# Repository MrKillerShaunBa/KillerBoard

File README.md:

# KillerBoard
Welcome to KillerBoard, a 65% wireless hot-swappable mechanical keyboard which is made in a sandwich mounted style. It has a 3d printed case, custom PCB and a ProMicro controller for it brains.

I got the motivation to make this when I saw other cool keyboards the people have built for ``#Highway``. Also, I loved making my [Hackpad](https://github.com/MrKillerShaunBa/BajajPad) and wanted to try making something which was bigger, better and wireless of-course.

## Featues

- 65% compact layout
- Wireless, uses Promicro Controller
- ZMK firmware
- Hotswappable
- Brown tactile switches
- 6 deg typing angle
- 3D Printed case and plate
- Sandwich mount

## CAD

## PCB

## ZMK Keymap 

### BOM

| Product | Quantity | Source | Price(INR) | Price($) | Link |
| :-----: | :-----: | :-----: | :-----: | :-----: | :-----: |
| Keycaps | 1 | StacksKB | 1299 | 15.10 | [here](https://stackskb.com/store/veekos-gradient-keycaps-cherry-profile-135-keys/) |
| MX Style Switches | 25*3 | Genesispc | 2400 | 27.91 | [here](https://www.genesispc.in/products/c-equalz-x-tkc-kiwi-switches?variant=43389284286517) |
| Stabilizers | 1 | StacksKB | 1595 | 18.55 | [here](https://stackskb.com/store/durock-smokey-screw-in-stabilizers-v2/) |
| PCB | 5 | JLCPCB | | 11.05 | Includes Shipping (Used Coupon) |
| Case | 1 | Printing Legion | - | ~5 | Only shipping |
| Hotswap Sockets | 10*7 | Meckeys | 536 | 6.23 | [here](https://meckeys.com/shop/accessories/keyboard-accessories/key-switches/kailh-hot-swap-socket/) |
| 1N4148 Diodes | 10*7 | StacksKB | 105 | 1.22 | [here](https://stackskb.com/store/1n4148-through-hole-diode/) |
| ProMicro nRF52840 | 1 | Robu.in | 715 | 8.33| [here](https://robu.in/product/promicro-nrf52840-development-board/) |
| Slide Switch | 1 | Robu.in | 3 | 0.035 | [here](https://robu.in/product/ss-12f21g5-slide-1p2t-angled-switchheight5mm/) |
| Battery | 1 | Robu.in | 256 | 2.97 | [here](https://robu.in/product/wly602540-600mah-3-7v-single-cell-rechargeable-lipo-battery/) |
| PCB receptacle female | 1 | Amazon | 135 | 1.57 | [here](https://amzn.in/d/0Ydhh59) |
| PCB receptacle male | 2 | Robu.in | 68 | 0.79 | [here](https://robu.in/product/361019115sg107601-jiln-2-54x1-9machined-pin-header-1x15p-180-l7-65-upper-pinpoint0-46-bottom-pinpoint0-46-au1u-pps/) |
| Non-slip feet | 100 | Amazon | 130 | 1.51 | [here](https://amzn.in/d/hfOWean) |
| M3x25mm bolts | 12 | Robu | 167 | 1.93 | [here](https://robu.in/product/easymech-set-m3-x-25mm-socket-head-cap-allen-bolt-nut-12-pcs/) |
| M3x15mm bolts | 10 | EDS | 139  | 1.61 | [here](https://store.edsystems.in/thunderbolt-set-of-m3-x-15mm-socket-head-cap-black-(allen)-bolt-and-nut-(10-pcs)) | M3x4mm heatset insert | 25 | Robu | 82 | 0.95 | [here](https://robu.in/product/m3-x-4-mm-brass-heat-set-knurl-threaded-round-insert-nut-25-pcs/) |
| M3x4mm heatset inserts | 25 | Robu | 82 | 0.95 | [here](https://robu.in/product/m3-x-4-mm-brass-heat-set-knurl-threaded-round-insert-nut-25-pcs/) |

Total Cost: About $108-110

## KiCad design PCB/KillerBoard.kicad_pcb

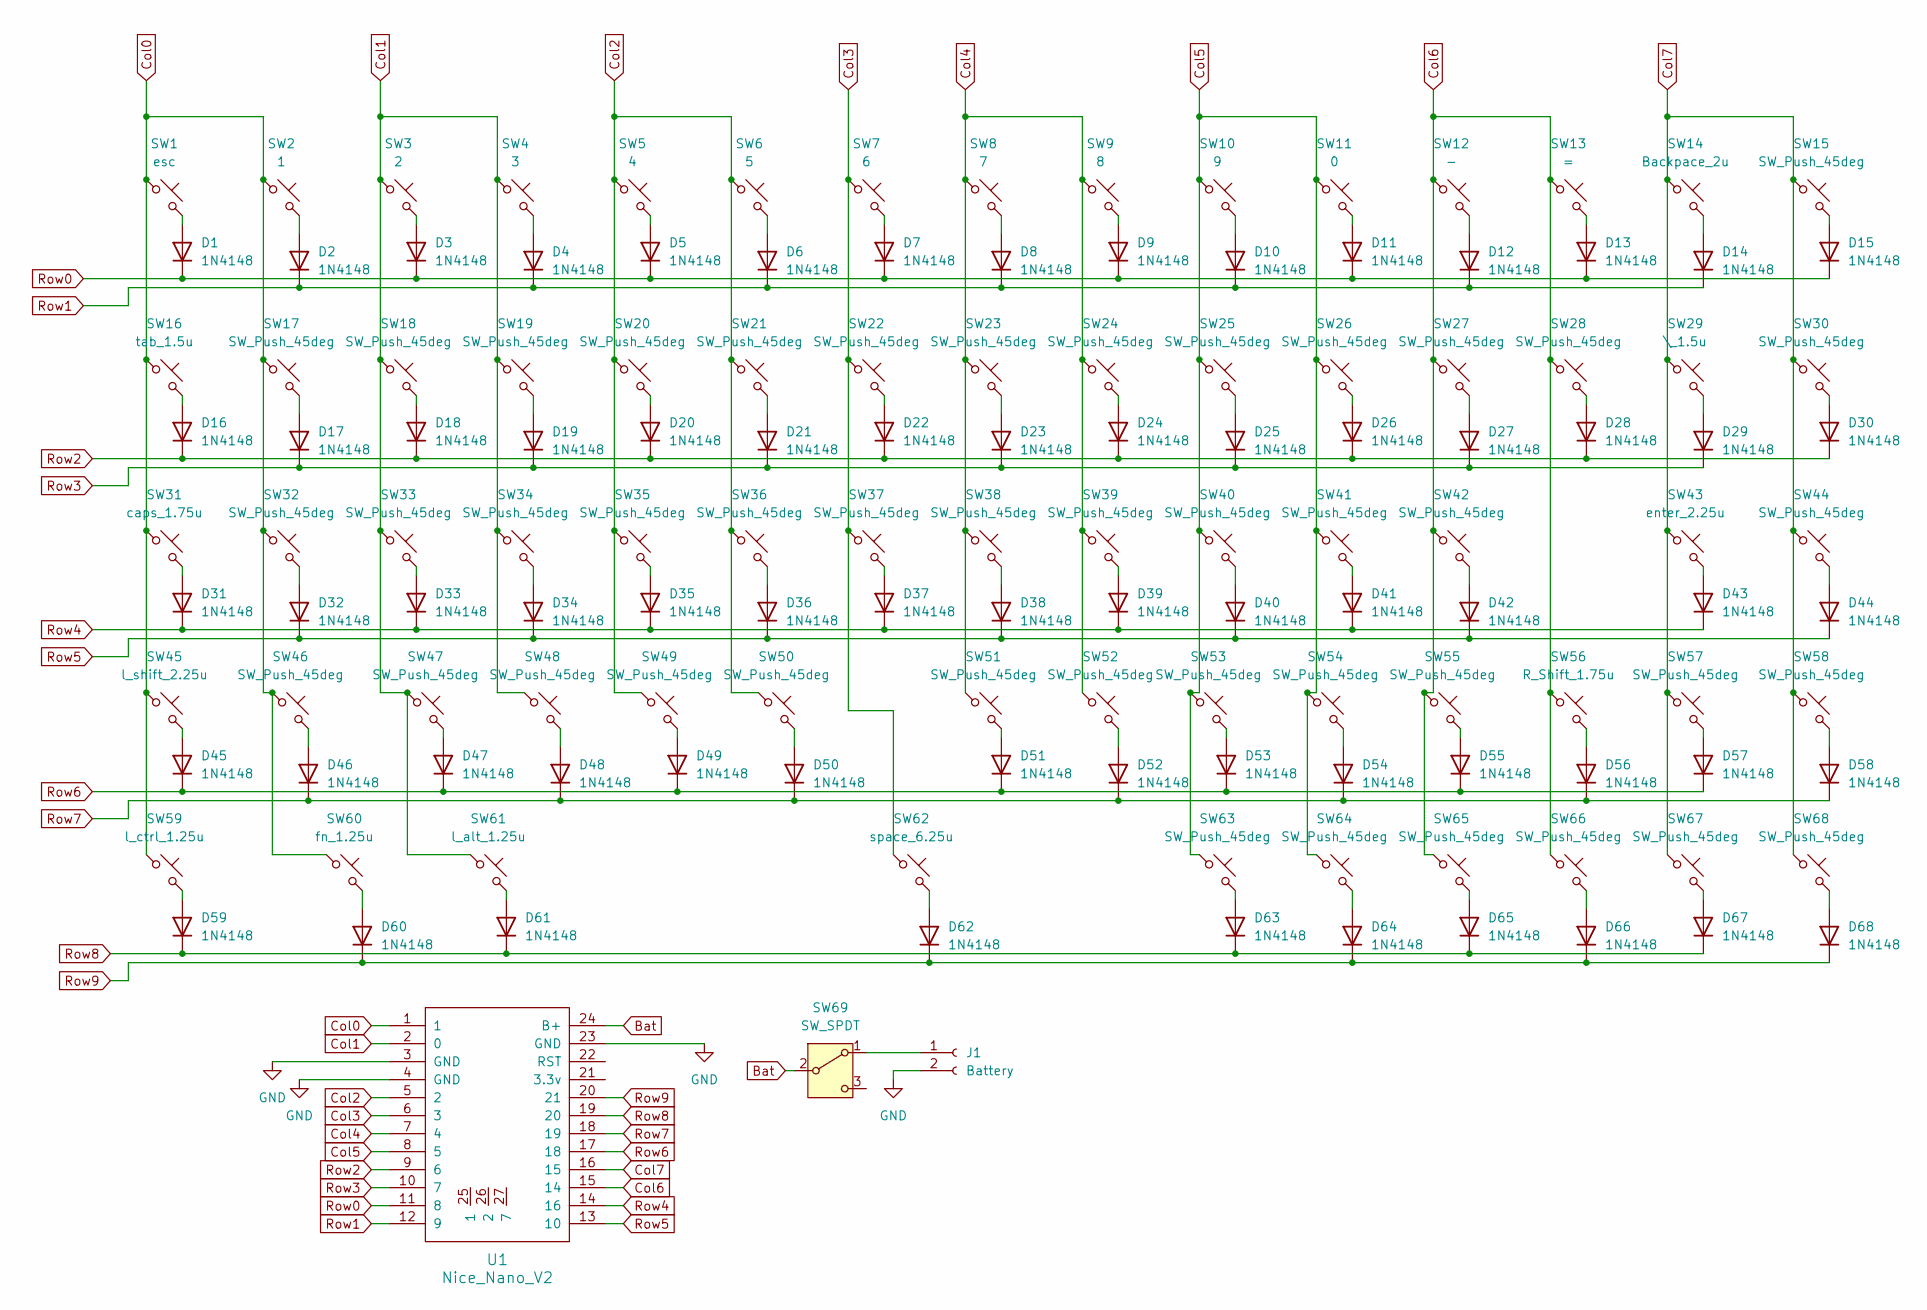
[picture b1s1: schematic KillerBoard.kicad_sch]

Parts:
D1, D2, D3, D4, D5, D6, D7, D8, D9, D10, D11, D12, D13, D14, D15, D16, D17, D18, D19, D20, D21, D22, D23, D24, D25, D26, D27, D28, D29, D30, D31, D32, D33, D34, D35, D36, D37, D38, D39, D40, D41, D42, D43, D44, D45, D46, D47, D48, D49, D50, D51, D52, D53, D54, D55, D56, D57, D58, D59, D60, D61, D62, D63, D64, D65, D66, D67, D68: 1N4148; D_DO-35_SOD27_P7.62mm_Horizontal
J1: Battery
SW1: esc; Hotswap_MX_Plated_1.00u
SW2: 1; Hotswap_MX_Plated_1.00u
SW3: 2; Hotswap_MX_Plated_1.00u
SW4: 3; Hotswap_MX_Plated_1.00u
SW5: 4; Hotswap_MX_Plated_1.00u
SW6: 5; Hotswap_MX_Plated_1.00u
SW7: 6; Hotswap_MX_Plated_1.00u
SW8: 7; Hotswap_MX_Plated_1.00u
SW9: 8; Hotswap_MX_Plated_1.00u
SW10: 9; Hotswap_MX_Plated_1.00u
SW11: 0; Hotswap_MX_Plated_1.00u
SW12: -; Hotswap_MX_Plated_1.00u
SW13: =; Hotswap_MX_Plated_1.00u
SW14: Backpace_2u; MX_Hotswap_2.00u
SW15, SW17, SW18, SW19, SW20, SW21, SW22, SW23, SW24, SW25, SW26, SW27, SW28, SW30, SW32, SW33, SW34, SW35, SW36, SW37, SW38, SW39, SW40, SW41, SW42, SW44, SW46, SW47, SW48, SW49, SW50, SW51, SW52, SW53, SW54, SW55, SW57, SW58, SW63, SW64, SW65, SW66, SW67, SW68: SW_Push_45deg; Hotswap_MX_Plated_1.00u
SW16: tab_1.5u; Hotswap_MX_Plated_1.50u
SW29: \_1.5u; Hotswap_MX_Plated_1.50u
SW31: caps_1.75u; Hotswap_MX_Plated_1.75u
SW43: enter_2.25u; MX_Hotswap_2.25u
SW45: l_shift_2.25u; MX_Hotswap_2.25u
SW56: R_Shift_1.75u; Hotswap_MX_Plated_1.75u
SW59: l_ctrl_1.25u; Hotswap_MX_Plated_1.25u
SW60: fn_1.25u; Hotswap_MX_Plated_1.25u
SW61: l_alt_1.25u; Hotswap_MX_Plated_1.25u
SW62: space_6.25u; MX_Hotswap_6.25u
SW69: SW_SPDT; Switch_K3-1204D
U1: Nice_Nano_V2

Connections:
Bat: SW69.2 (B), U1.24 (B+)
Col0: SW1.1, SW2.1, SW16.1, SW17.1, SW31.1, SW32.1, SW45.1, SW46.1, SW59.1, SW60.1, U1.1
Col1: SW3.1, SW4.1, SW18.1, SW19.1, SW33.1, SW34.1, SW47.1, SW48.1, SW61.1, U1.2 (0)
Col2: SW5.1, SW6.1, SW20.1, SW21.1, SW35.1, SW36.1, SW49.1, SW50.1, U1.5 (2)
Col3: SW7.1, SW22.1, SW37.1, SW62.1, U1.6 (3)
Col4: SW8.1, SW9.1, SW23.1, SW24.1, SW38.1, SW39.1, SW51.1, SW52.1, U1.7 (4)
Col5: SW10.1, SW11.1, SW25.1, SW26.1, SW40.1, SW41.1, SW53.1, SW54.1, SW63.1, SW64.1, U1.8 (5)
Col6: SW12.1, SW13.1, SW27.1, SW28.1, SW42.1, SW55.1, SW56.1, SW65.1, SW66.1, U1.15 (14)
Col7: SW14.1, SW15.1, SW29.1, SW30.1, SW43.1, SW44.1, SW57.1, SW58.1, SW67.1, SW68.1, U1.16 (15)
GND: J1.2, U1.3 (GND), U1.4 (GND), U1.23 (GND)
unnamed: D1.2 (A), SW1.2
unnamed: D2.2 (A), SW2.2
unnamed: D3.2 (A), SW3.2
unnamed: D4.2 (A), SW4.2
unnamed: D5.2 (A), SW5.2
unnamed: D6.2 (A), SW6.2
unnamed: D7.2 (A), SW7.2
unnamed: D8.2 (A), SW8.2
unnamed: D9.2 (A), SW9.2
unnamed: D10.2 (A), SW10.2
unnamed: D11.2 (A), SW11.2
unnamed: D12.2 (A), SW12.2
unnamed: D13.2 (A), SW13.2
unnamed: D14.2 (A), SW14.2
unnamed: D15.2 (A), SW15.2
unnamed: D16.2 (A), SW16.2
unnamed: D17.2 (A), SW17.2
unnamed: D18.2 (A), SW18.2
unnamed: D19.2 (A), SW19.2
unnamed: D20.2 (A), SW20.2
unnamed: D21.2 (A), SW21.2
unnamed: D22.2 (A), SW22.2
unnamed: D23.2 (A), SW23.2
unnamed: D24.2 (A), SW24.2
unnamed: D25.2 (A), SW25.2
unnamed: D26.2 (A), SW26.2
unnamed: D27.2 (A), SW27.2
unnamed: D28.2 (A), SW28.2
unnamed: D29.2 (A), SW29.2
unnamed: D30.2 (A), SW30.2
unnamed: D31.2 (A), SW31.2
unnamed: D32.2 (A), SW32.2
unnamed: D33.2 (A), SW33.2
unnamed: D34.2 (A), SW34.2
unnamed: D35.2 (A), SW35.2
unnamed: D36.2 (A), SW36.2
unnamed: D37.2 (A), SW37.2
unnamed: D38.2 (A), SW38.2
unnamed: D39.2 (A), SW39.2
unnamed: D40.2 (A), SW40.2
unnamed: D41.2 (A), SW41.2
unnamed: D42.2 (A), SW42.2
unnamed: D43.2 (A), SW43.2
unnamed: D44.2 (A), SW44.2
unnamed: D45.2 (A), SW45.2
unnamed: D46.2 (A), SW46.2
unnamed: D47.2 (A), SW47.2
unnamed: D48.2 (A), SW48.2
unnamed: D49.2 (A), SW49.2
unnamed: D50.2 (A), SW50.2
unnamed: D51.2 (A), SW51.2
unnamed: D52.2 (A), SW52.2
unnamed: D53.2 (A), SW53.2
unnamed: D54.2 (A), SW54.2
unnamed: D55.2 (A), SW55.2
unnamed: D56.2 (A), SW56.2
unnamed: D57.2 (A), SW57.2
unnamed: D58.2 (A), SW58.2
unnamed: D59.2 (A), SW59.2
unnamed: D60.2 (A), SW60.2
unnamed: D61.2 (A), SW61.2
unnamed: D62.2 (A), SW62.2
unnamed: D63.2 (A), SW63.2
unnamed: D64.2 (A), SW64.2
unnamed: D65.2 (A), SW65.2
unnamed: D66.2 (A), SW66.2
unnamed: D67.2 (A), SW67.2
unnamed: D68.2 (A), SW68.2
unnamed: J1.1, SW69.1 (A)
Row0: D1.1 (K), D3.1 (K), D5.1 (K), D7.1 (K), D9.1 (K), D11.1 (K), D13.1 (K), D15.1 (K), U1.11 (8)
Row1: D2.1 (K), D4.1 (K), D6.1 (K), D8.1 (K), D10.1 (K), D12.1 (K), D14.1 (K), U1.12 (9)
Row2: D16.1 (K), D18.1 (K), D20.1 (K), D22.1 (K), D24.1 (K), D26.1 (K), D28.1 (K), D30.1 (K), U1.9 (6)
Row3: D17.1 (K), D19.1 (K), D21.1 (K), D23.1 (K), D25.1 (K), D27.1 (K), D29.1 (K), U1.10 (7)
Row4: D31.1 (K), D33.1 (K), D35.1 (K), D37.1 (K), D39.1 (K), D41.1 (K), D43.1 (K), U1.14 (16)
Row5: D32.1 (K), D34.1 (K), D36.1 (K), D38.1 (K), D40.1 (K), D42.1 (K), D44.1 (K), U1.13 (10)
Row6: D45.1 (K), D47.1 (K), D49.1 (K), D51.1 (K), D53.1 (K), D55.1 (K), D57.1 (K), U1.17 (18)
Row7: D46.1 (K), D48.1 (K), D50.1 (K), D52.1 (K), D54.1 (K), D56.1 (K), D58.1 (K), U1.18 (19)
Row8: D59.1 (K), D61.1 (K), D63.1 (K), D65.1 (K), D67.1 (K), U1.19 (20)
Row9: D60.1 (K), D62.1 (K), D64.1 (K), D66.1 (K), D68.1 (K), U1.20 (21)

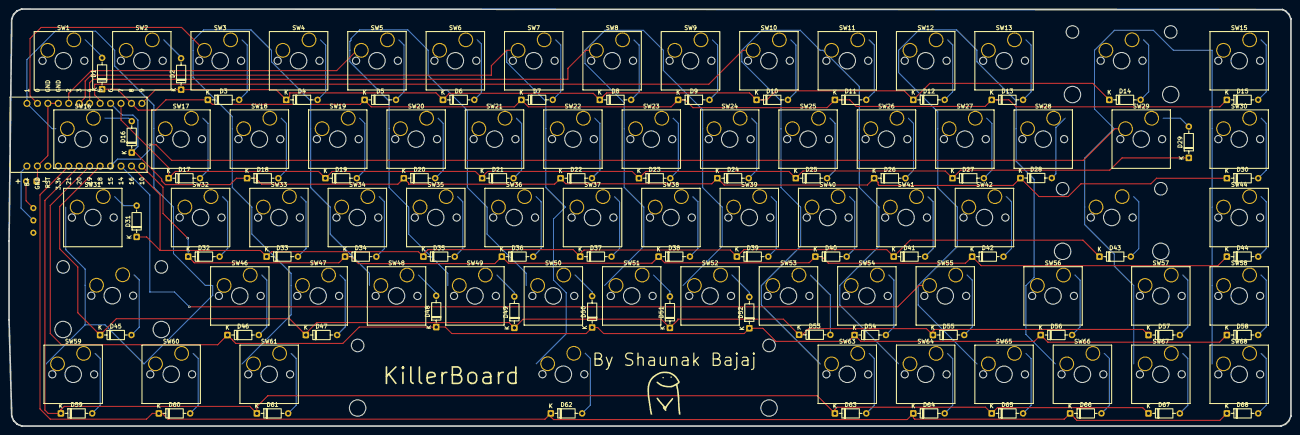
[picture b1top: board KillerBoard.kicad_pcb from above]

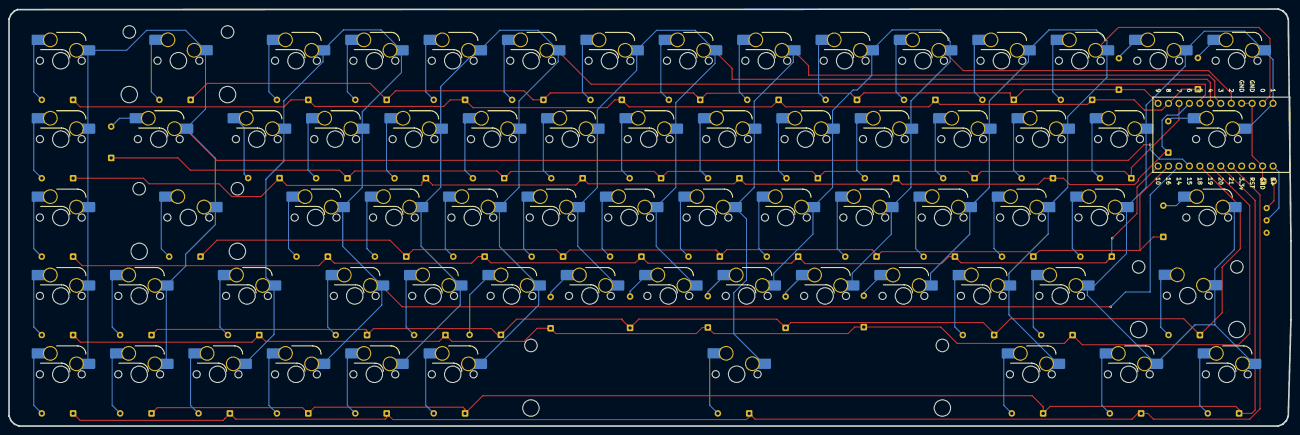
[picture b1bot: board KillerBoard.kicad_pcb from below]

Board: 2 copper layers, 311.5 x 101.3 mm, 139 parts (2 on the bottom side), 89 nets.

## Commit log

2025-07-22 Added firmware
2025-07-22 Create del
